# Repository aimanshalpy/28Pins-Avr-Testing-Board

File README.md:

# 28Pins-Avr-Testing-Board
Testing board for AVR 28 pins with power regulator and USB
# Donate by PayPal
# paypal.me/AymanShalaby

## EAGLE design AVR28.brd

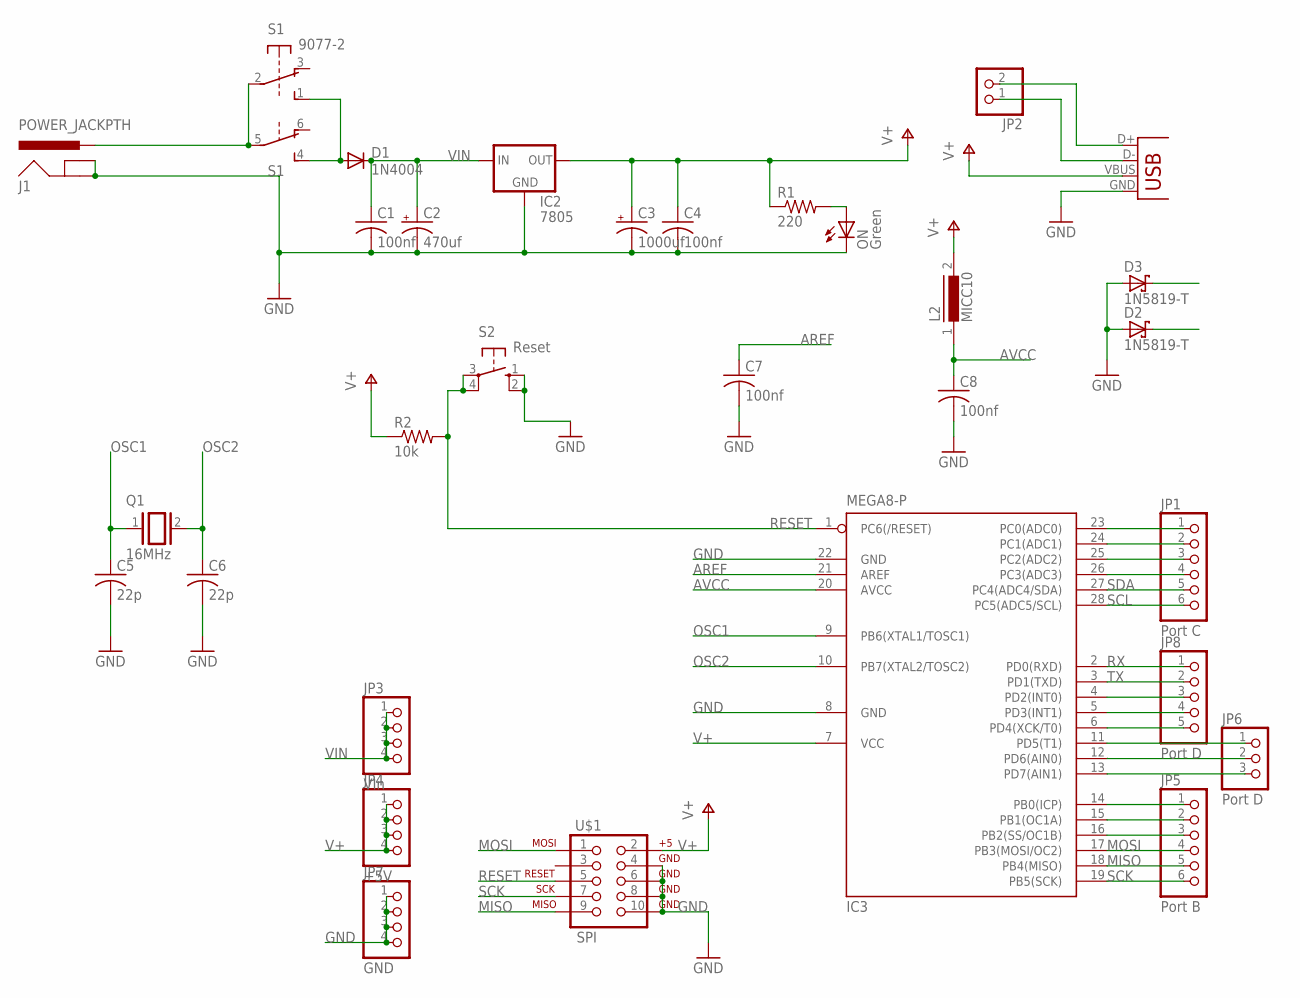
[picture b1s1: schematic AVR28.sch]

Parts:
C1, C4, C7, C8: 100nf; C050-025X075
C2: 470uf; E3,5-8
C3: 1000uf; E3,5-8
C5, C6: 22p; C050-025X075
D1: 1N4004; DO41-10
D2, D3: 1N5819-T; DO41-7.6
IC2: 7805; 78XXL
IC3: MEGA8-P; DIL28-3
J1: POWER_JACKPTH; POWER_JACK_PTH
JP1: Port C; 1X06
JP2: PINHD-1X2; 1X02
JP3: VIn; 1X04
JP4: +5V; 1X04
JP5: Port B; 1X06
JP6: Port D; 1X03
JP7: GND; 1X04
JP8: Port D; 1X05
L2: MICC10
ON: Green; LED3MM
Q1: 16MHz; QS
R1: 220; 0207/10
R2: 10k; 0207/10
S1: 9077-2
S2: Reset; B3F-10XX
U$1: SPI; 2X5-SHROUDED_LOCK
X1: USBPTH; USB-B-PTH

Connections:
AREF: C7.1, IC3.21 (AREF)
AVCC: C8.1, IC3.20 (AVCC), L2.1
D+: D2.C, JP2.2, X1.D+
D-: D3.C, JP2.1, X1.D-
GND: C1.2, C2.-, C3.-, C4.2, C5.2, C6.2, C7.2, C8.2, D2.A, D3.A, IC2.GND, IC3.8 (GND), IC3.22 (GND), J1.GND, J1.GNDBREAK, JP7.1, JP7.2, JP7.3, JP7.4, ON.K (C), S2.1 (S), S2.2 (S1), U$1.4, U$1.6, U$1.8, U$1.10, X1.GND
MISO: IC3.18 (PB4(MISO)), JP5.5, U$1.9
MOSI: IC3.17 (PB3(MOSI/OC2)), JP5.4, U$1.1
unnamed: J1.PWR, S1.2, S1.5
unnamed: D1.A, S1.1 (S), S1.4 (S)
unnamed: IC3.23 (PC0(ADC0)), JP1.1
unnamed: ON.A, R1.2
unnamed: IC3.24 (PC1(ADC1)), JP1.2
unnamed: IC3.25 (PC2(ADC2)), JP1.3
unnamed: IC3.26 (PC3(ADC3)), JP1.4
unnamed: IC3.4 (PD2(INT0)), JP8.3
unnamed: IC3.5 (PD3(INT1)), JP8.4
unnamed: IC3.6 (PD4(XCK/T0)), JP8.5
unnamed: IC3.11 (PD5(T1)), JP6.1
unnamed: IC3.12 (PD6(AIN0)), JP6.2
unnamed: IC3.13 (PD7(AIN1)), JP6.3
unnamed: IC3.14 (PB0(ICP)), JP5.1
unnamed: IC3.15 (PB1(OC1A)), JP5.2
unnamed: IC3.16 (PB2(SS/OC1B)), JP5.3
OSC1: C5.1, IC3.9 (PB6(XTAL1/TOSC1)), Q1.1
OSC2: C6.1, IC3.10 (PB7(XTAL2/TOSC2)), Q1.2
RESET: IC3.1 (PC6(/RESET)), R2.2, S2.3, S2.4 (P1), U$1.5
RX: IC3.2 (PD0(RXD)), JP8.1
SCK: IC3.19 (PB5(SCK)), JP5.6, U$1.7
SCL: IC3.28 (PC5(ADC5/SCL)), JP1.6
SDA: IC3.27 (PC4(ADC4/SDA)), JP1.5
TX: IC3.3 (PD1(TXD)), JP8.2
V+: C3.+, C4.1, IC2.OUT, IC3.7 (VCC), JP4.1, JP4.2, JP4.3, JP4.4, L2.2, R1.1, R2.1, U$1.2, X1.VBUS
VIN: C1.1, C2.+, D1.C, IC2.IN, JP3.1, JP3.2, JP3.3, JP3.4

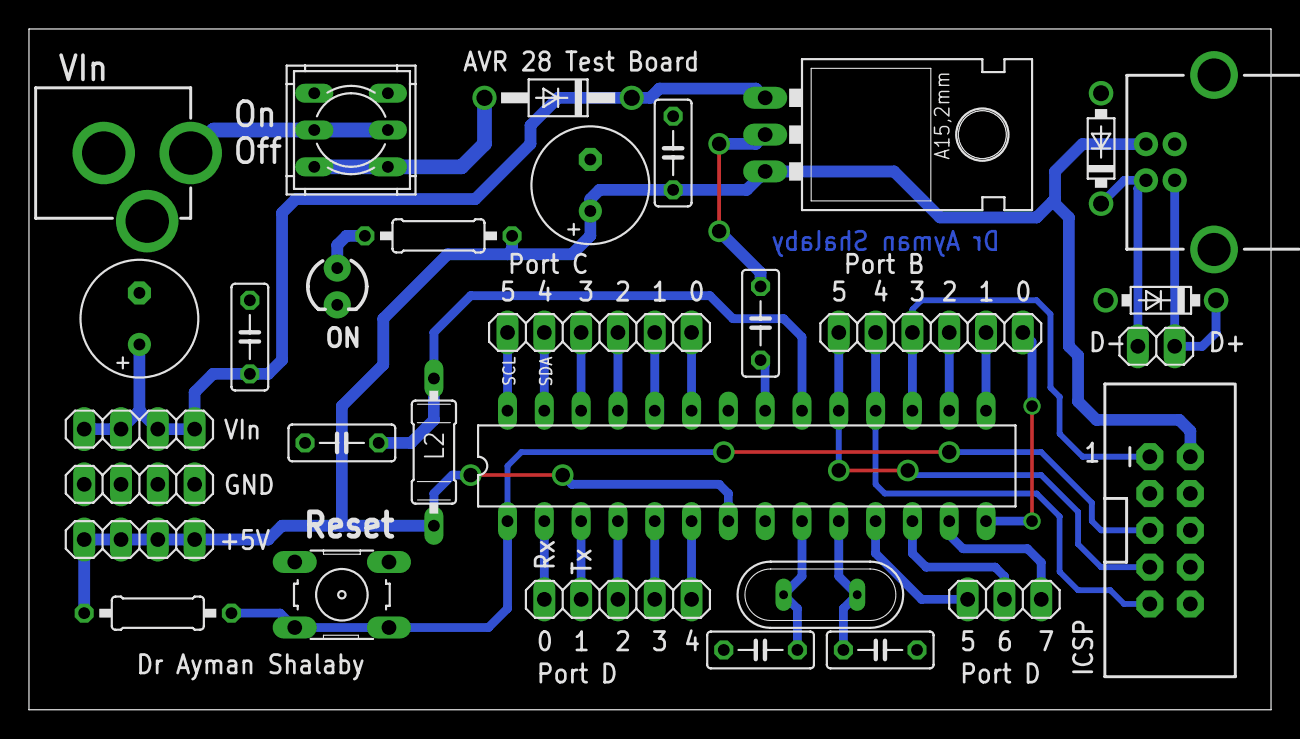
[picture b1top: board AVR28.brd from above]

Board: 2 copper layers, 85.7 x 47.0 mm, 31 parts (0 on the bottom side), 33 nets.

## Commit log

2018-02-16 Add files via upload
    Testing board for AVR 28 pins with power regulator and USB, ATMega 8, 168, 328

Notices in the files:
parts and their libraries:
SparkFun: Licensing: CC v3.0 Share-Alike You are welcome to use this library for commercial purposes.
